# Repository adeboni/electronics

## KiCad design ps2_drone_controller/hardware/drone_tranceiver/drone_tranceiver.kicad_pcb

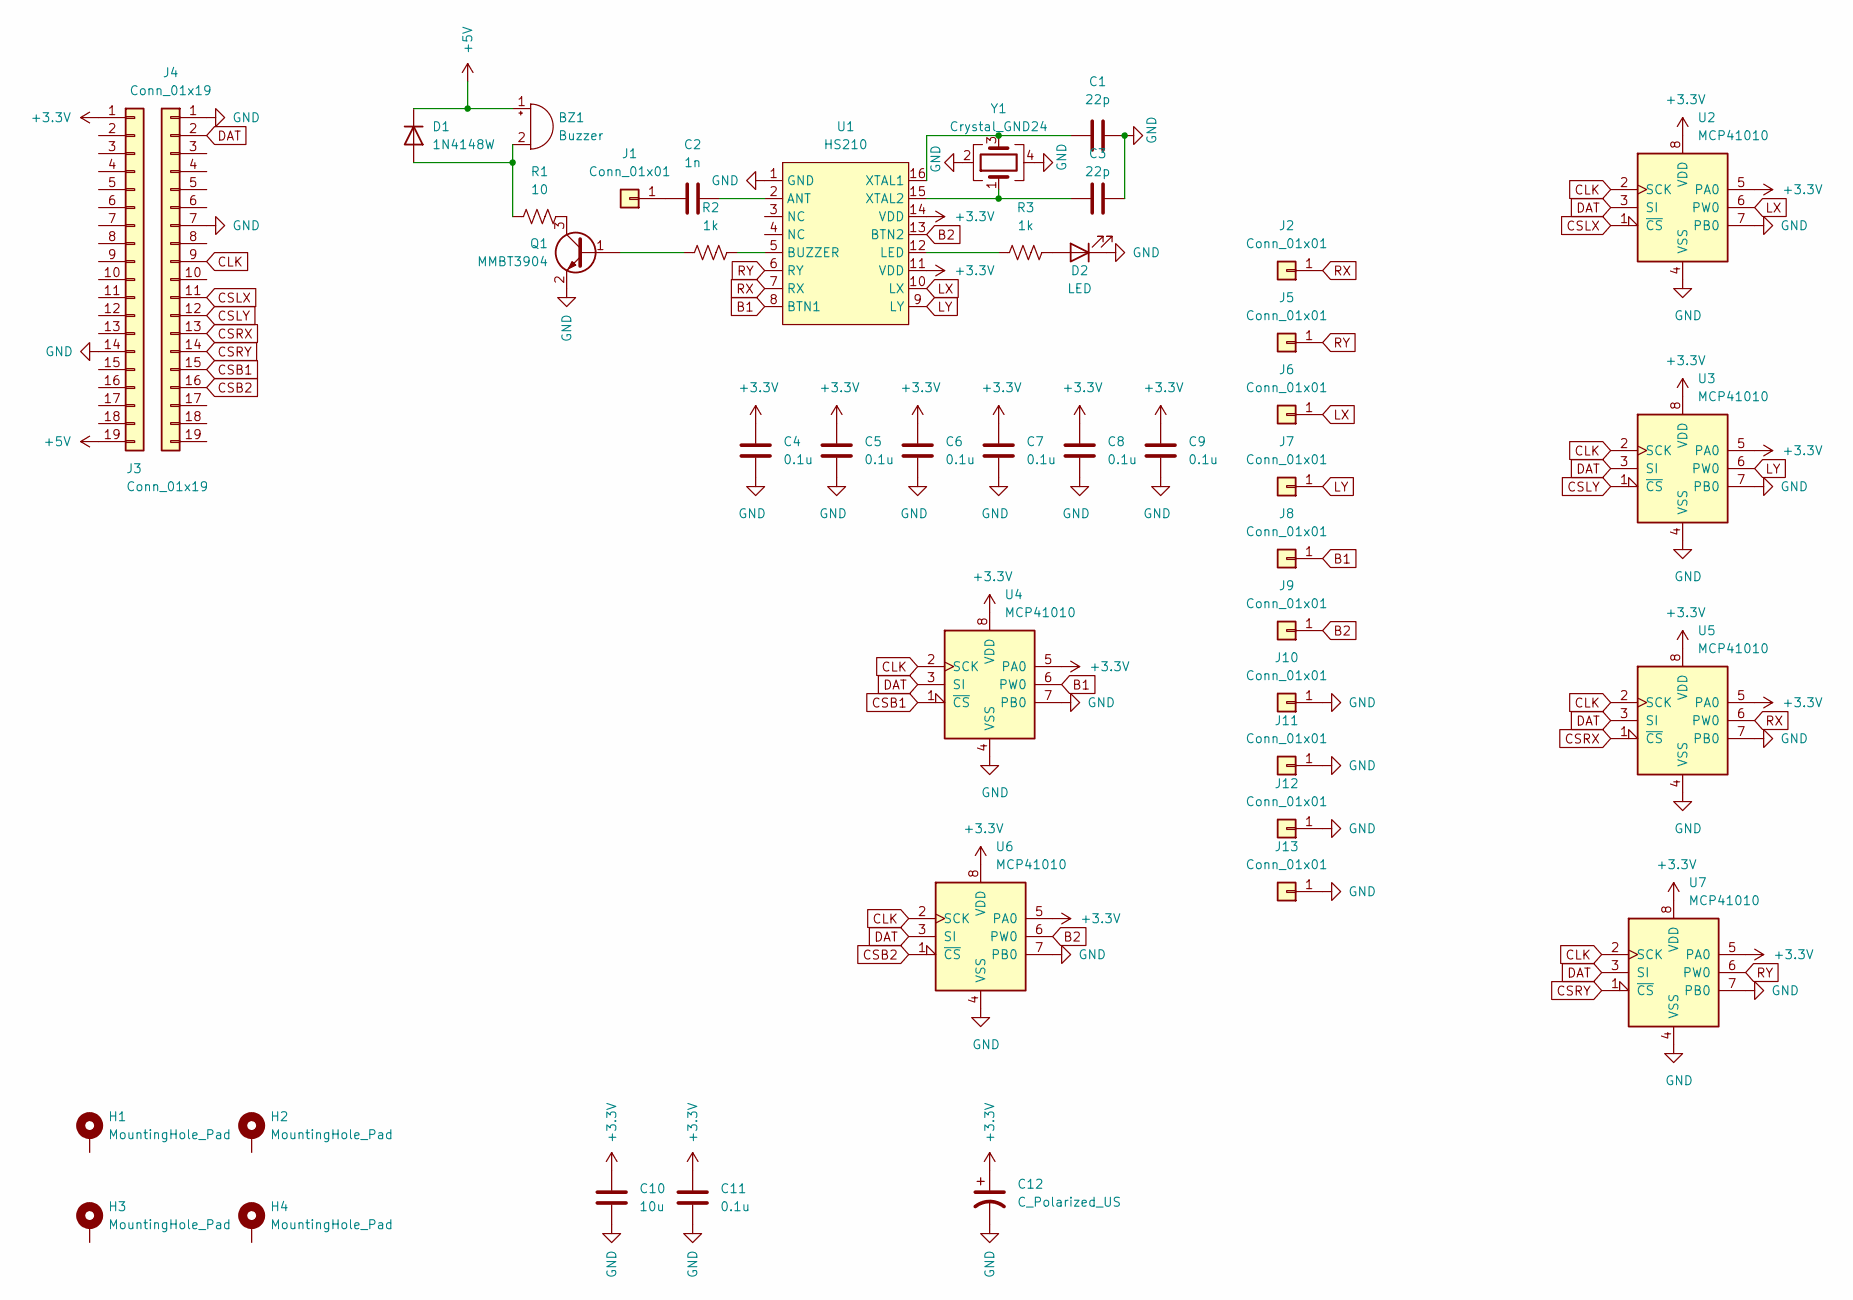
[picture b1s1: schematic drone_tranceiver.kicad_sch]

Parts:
BZ1: Buzzer; Buzzer_12x9.5RM7.6
C1, C3: 22p; C_0603_1608Metric
C2: 1n; C_0603_1608Metric
C4, C5, C6, C7, C8, C9, C11: 0.1u; C_0603_1608Metric
C10: 10u; C_0603_1608Metric
C12: C_Polarized_US; CP_Radial_D10.0mm_P5.00mm
D1: 1N4148W; D_SOD-123
D2: LED; LED_D3.0mm
H1, H2, H3, H4: MountingHole_Pad; MountingHole_3.2mm_M3_DIN965_Pad_TopBottom
J1, J2, J5, J6, J7, J8, J9, J10, J11, J12, J13: Conn_01x01; PinSocket_1x01_P2.54mm_Vertical
J3, J4: Conn_01x19; PinSocket_1x19_P2.54mm_Vertical
Q1: MMBT3904; SOT-23
R1: 10; R_0603_1608Metric
R2, R3: 1k; R_0603_1608Metric
U1: HS210; SOIC-16_3.9x9.9mm_P1.27mm
U2, U3, U4, U5, U6, U7: MCP41010; SOIC-8_3.9x4.9mm_P1.27mm
Y1: Crystal_GND24; Crystal_SMD_3225-4Pin_3.2x2.5mm

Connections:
+3.3V: C4.2, C5.2, C6.2, C7.2, C8.2, C9.2, C10.1, C11.1, C12.1, J3.1, U1.11 (VDD), U1.14 (VDD), U2.5 (PA0), U2.8 (VDD), U3.5 (PA0), U3.8 (VDD), U4.5 (PA0), U4.8 (VDD), U5.5 (PA0), U5.8 (VDD), U6.5 (PA0), U6.8 (VDD), U7.5 (PA0), U7.8 (VDD)
+5V: BZ1.1 (-), D1.1 (K), J3.19
B1: J8.1, U1.8 (BTN1), U4.6 (PW0)
B2: J9.1, U1.13 (BTN2), U6.6 (PW0)
CLK: J4.9, U2.2 (SCK), U3.2 (SCK), U4.2 (SCK), U5.2 (SCK), U6.2 (SCK), U7.2 (SCK)
CSB1: J4.15, U4.1 (~CS)
CSB2: J4.16, U6.1 (~CS)
CSLX: J4.11, U2.1 (~CS)
CSLY: J4.12, U3.1 (~CS)
CSRX: J4.13, U5.1 (~CS)
CSRY: J4.14, U7.1 (~CS)
DAT: J4.2, U2.3 (SI), U3.3 (SI), U4.3 (SI), U5.3 (SI), U6.3 (SI), U7.3 (SI)
GND: C1.1, C3.1, C4.1, C5.1, C6.1, C7.1, C8.1, C9.1, C10.2, C11.2, C12.2, D2.1 (K), J3.14, J4.1, J4.7, J10.1, J11.1, J12.1, J13.1, Q1.2 (E), U1.1 (GND), U2.4 (VSS), U2.7 (PB0), U3.4 (VSS), U3.7 (PB0), U4.4 (VSS), U4.7 (PB0), U5.4 (VSS), U5.7 (PB0), U6.4 (VSS), U6.7 (PB0), U7.4 (VSS), U7.7 (PB0), Y1.2, Y1.4
LX: J6.1, U1.10 (LX), U2.6 (PW0)
LY: J7.1, U1.9 (LY), U3.6 (PW0)
unnamed: BZ1.2 (+), D1.2 (A), R1.1
unnamed: C1.2, U1.16 (XTAL1), Y1.3
unnamed: C2.1, J1.1
unnamed: C2.2, U1.2 (ANT)
unnamed: C3.2, U1.15 (XTAL2), Y1.1
unnamed: D2.2 (A), R3.2
unnamed: Q1.1 (B), R2.1
unnamed: Q1.3 (C), R1.2
unnamed: R2.2, U1.5 (BUZZER)
unnamed: R3.1, U1.12 (LED)
RX: J2.1, U1.7 (RX), U5.6 (PW0)
RY: J5.1, U1.6 (RY), U7.6 (PW0)

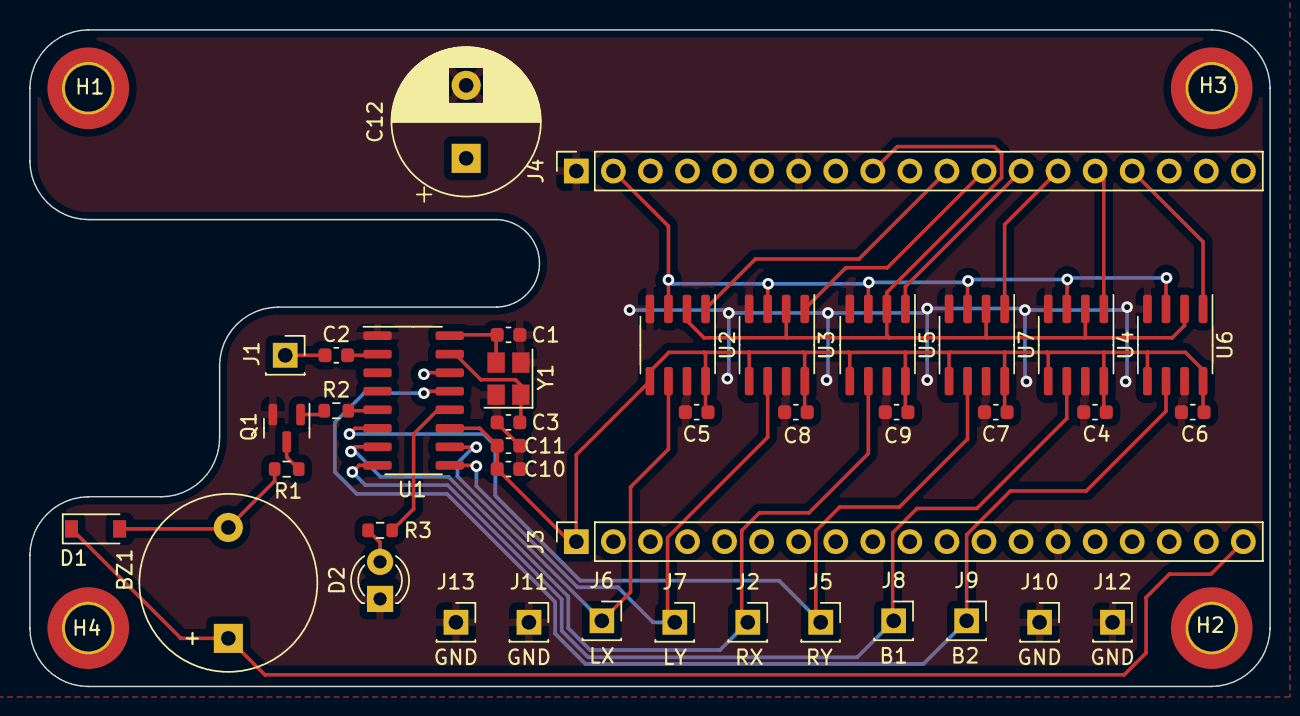
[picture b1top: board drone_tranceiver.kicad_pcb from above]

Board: 2 copper layers, 85.0 x 45.0 mm, 44 parts (0 on the bottom side), 27 nets.

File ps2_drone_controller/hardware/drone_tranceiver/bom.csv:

Comment,Designator,Footprint,LCSC Part Number
1N4148W,D1,D_SOD-123,C81598
0.1u,"C8,C7,C6,C4,C5,C11,C9",C_0603_1608Metric,C14663
Crystal_GND24,Y1,Crystal_SMD_3225-4Pin_3.2x2.5mm,C13738
MCP41010,"U2,U7,U3,U4,U5,U6",SOIC-8_3.9x4.9mm_P1.27mm,C136395
1k,"R3,R2",R_0603_1608Metric,C21190
22p,"C1,C3",C_0603_1608Metric,C1653
10u,C10,C_0603_1608Metric,C19702
1n,C2,C_0603_1608Metric,C1588
MMBT3904,Q1,SOT-23,C20526
10,R1,R_0603_1608Metric,C22859

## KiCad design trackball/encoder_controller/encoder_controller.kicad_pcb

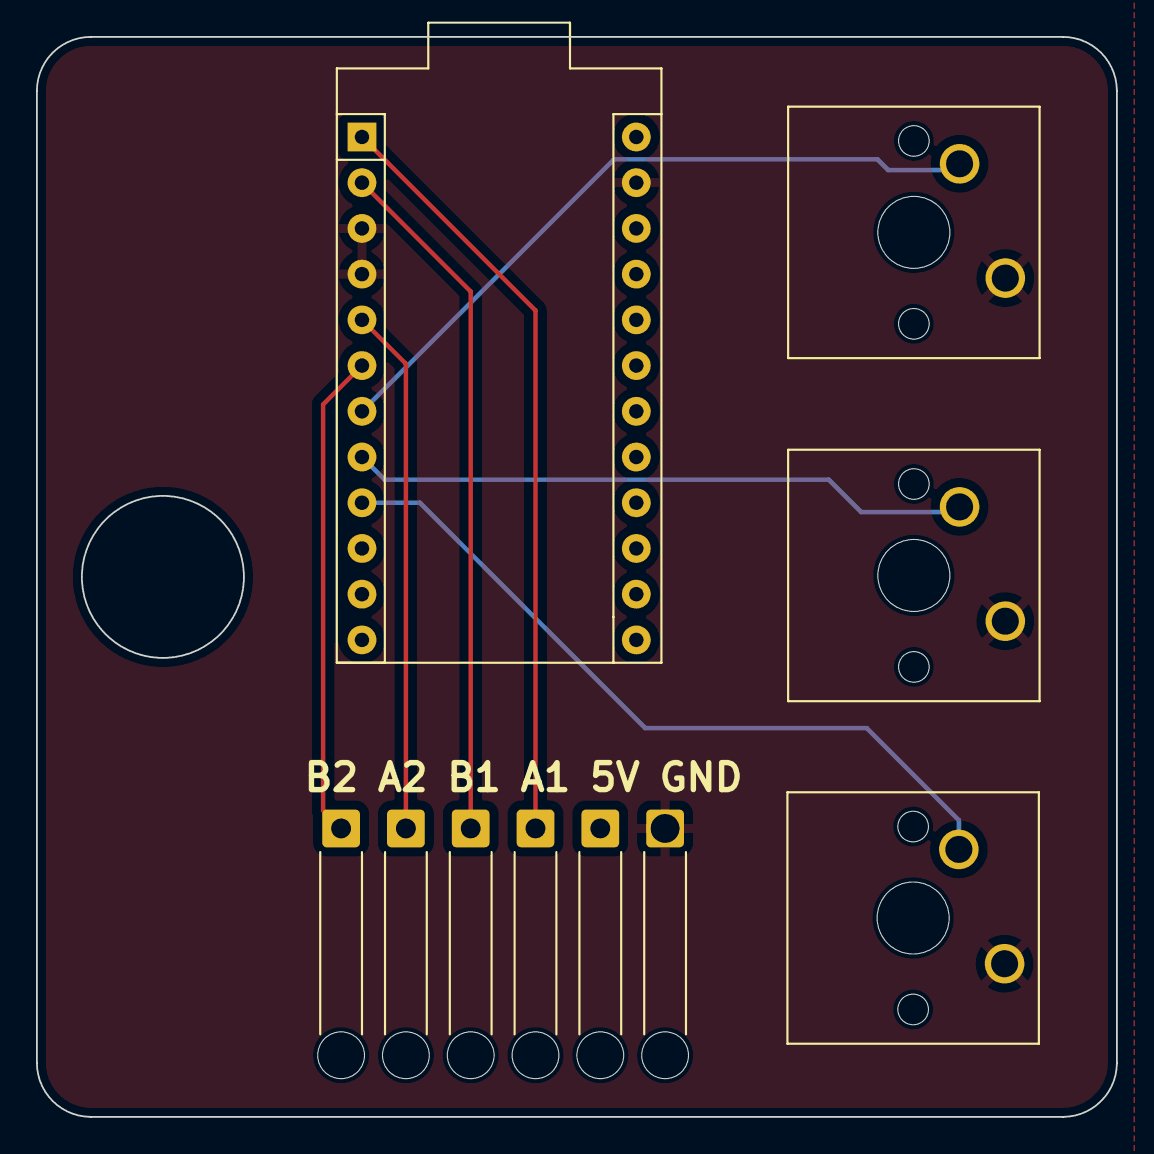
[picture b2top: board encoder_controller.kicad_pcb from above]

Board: 2 copper layers, 60.0 x 60.0 mm, 10 parts (0 on the bottom side), 9 nets.

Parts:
J1, J6, J8, J9, J10, J11: Conn_01x01; SolderWire-0.5sqmm_1x01_D0.9mm_OD2.1mm_Relief
SW1, SW2, SW3: SW_Push; SW_Cherry_MX_1.00u_PCB
U1: Sparkfun_Pro_Micro

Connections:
+5V: J9.1, U1.21 (VCC)
A1: J10.1, U1.1 (D1/TX)
A2: J8.1, U1.5 (D2)
B1: J11.1, U1.2 (D0/RX)
B2: J6.1, U1.6 (~D3)
GND: J1.1, SW1.1, SW2.1, SW3.1, U1.3 (GND), U1.4 (GND), U1.23 (GND)
LEFT: SW1.2, U1.7 (D4/A6)
MIDDLE: SW2.2, U1.8 (~D5)
RIGHT: SW3.2, U1.9 (~D6/A7)
